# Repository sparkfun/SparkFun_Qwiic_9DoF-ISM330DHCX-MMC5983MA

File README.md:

SparkFun Qwiic 9DoF ISM330DHCX, MMC5983MA
========================================

[*SparkFun_Qwiic_9DoF-ISM330DHCX-MMC5983MA (19895)*](https://www.sparkfun.com/products/19895)

The SparkFun 9DoF IMU Breakout - ISM330DHCX, MMC5983MA (Qwiic) combines the high-performance ISM330DHCX 3D digital accelerometer and gyroscope from STMicroelectronics with the highly sensitive triple-axis magnetometer by MEMSIC to give you an ultra powerful, easy to use, Qwiic enabled breakout board. 

With a full scale acceleration range of ±2/±4/±8/±16 g and a wide angular rate range of ±125/±250/±500/±1000/±2000/±4000 dps, as well as an unmatched set of embedded features (Machine Learning Core, programmable FSM, FIFO, sensor hub, event decoding and interrupts), the ISM330DHCX delivers high performance at very low power. Add to that the MMC5983MA, which can measure magnetic fields within the full scale range of &#177;8 Gauss (G), with 0.25mG/0.0625mG per LSB resolution at 16bits/18bits operation mode and 0.4 mG total RMS noise level and you've got 9 Degrees of Freedom on one tiny little breakout board. 

Utilizing our handy Qwiic system, no soldering is required to connect it to the rest of your system. However, we still have broken out 0.1"-spaced pins in case you prefer to use a breadboard.  
  
Repository Contents
-------------------

* **/Documentation** - Data sheets, additional product information
* **/Hardware** - Eagle design files (.brd, .sch)
* **/Production** - Production panel files (.brd)

Documentation
--------------

* **[6DoF ISM330DHCX Library](https://github.com/sparkfun/SparkFun_6DoF_ISM330DHCX_Arduino_Library)** - Arduino library for the SparkFun Qwiic 6DoF ISM330DHCX.
* **[MMC5983MA Magnetometer Library](https://github.com/sparkfun/SparkFun_MMC5983MA_Magnetometer_Arduino_Library)** - Arduino library for the SparkFun Qwiic MMC5983MA Magnetometer.
* **[Hookup Guide](https://learn.sparkfun.com/tutorials/2616)** - Basic hookup guide for the SparkFun Qwiic 9DoF-ISM330DHCX-MMC5983MA.

License Information
-------------------

This product is _**open source**_! 

Please review the LICENSE.md file for license information. 

If you have any questions or concerns on licensing, please contact technical support on our [SparkFun forums](https://forum.sparkfun.com/viewforum.php?f=152).

Distributed as-is; no warranty is given.

- Your friends at SparkFun.

_<COLLABORATION CREDIT>_

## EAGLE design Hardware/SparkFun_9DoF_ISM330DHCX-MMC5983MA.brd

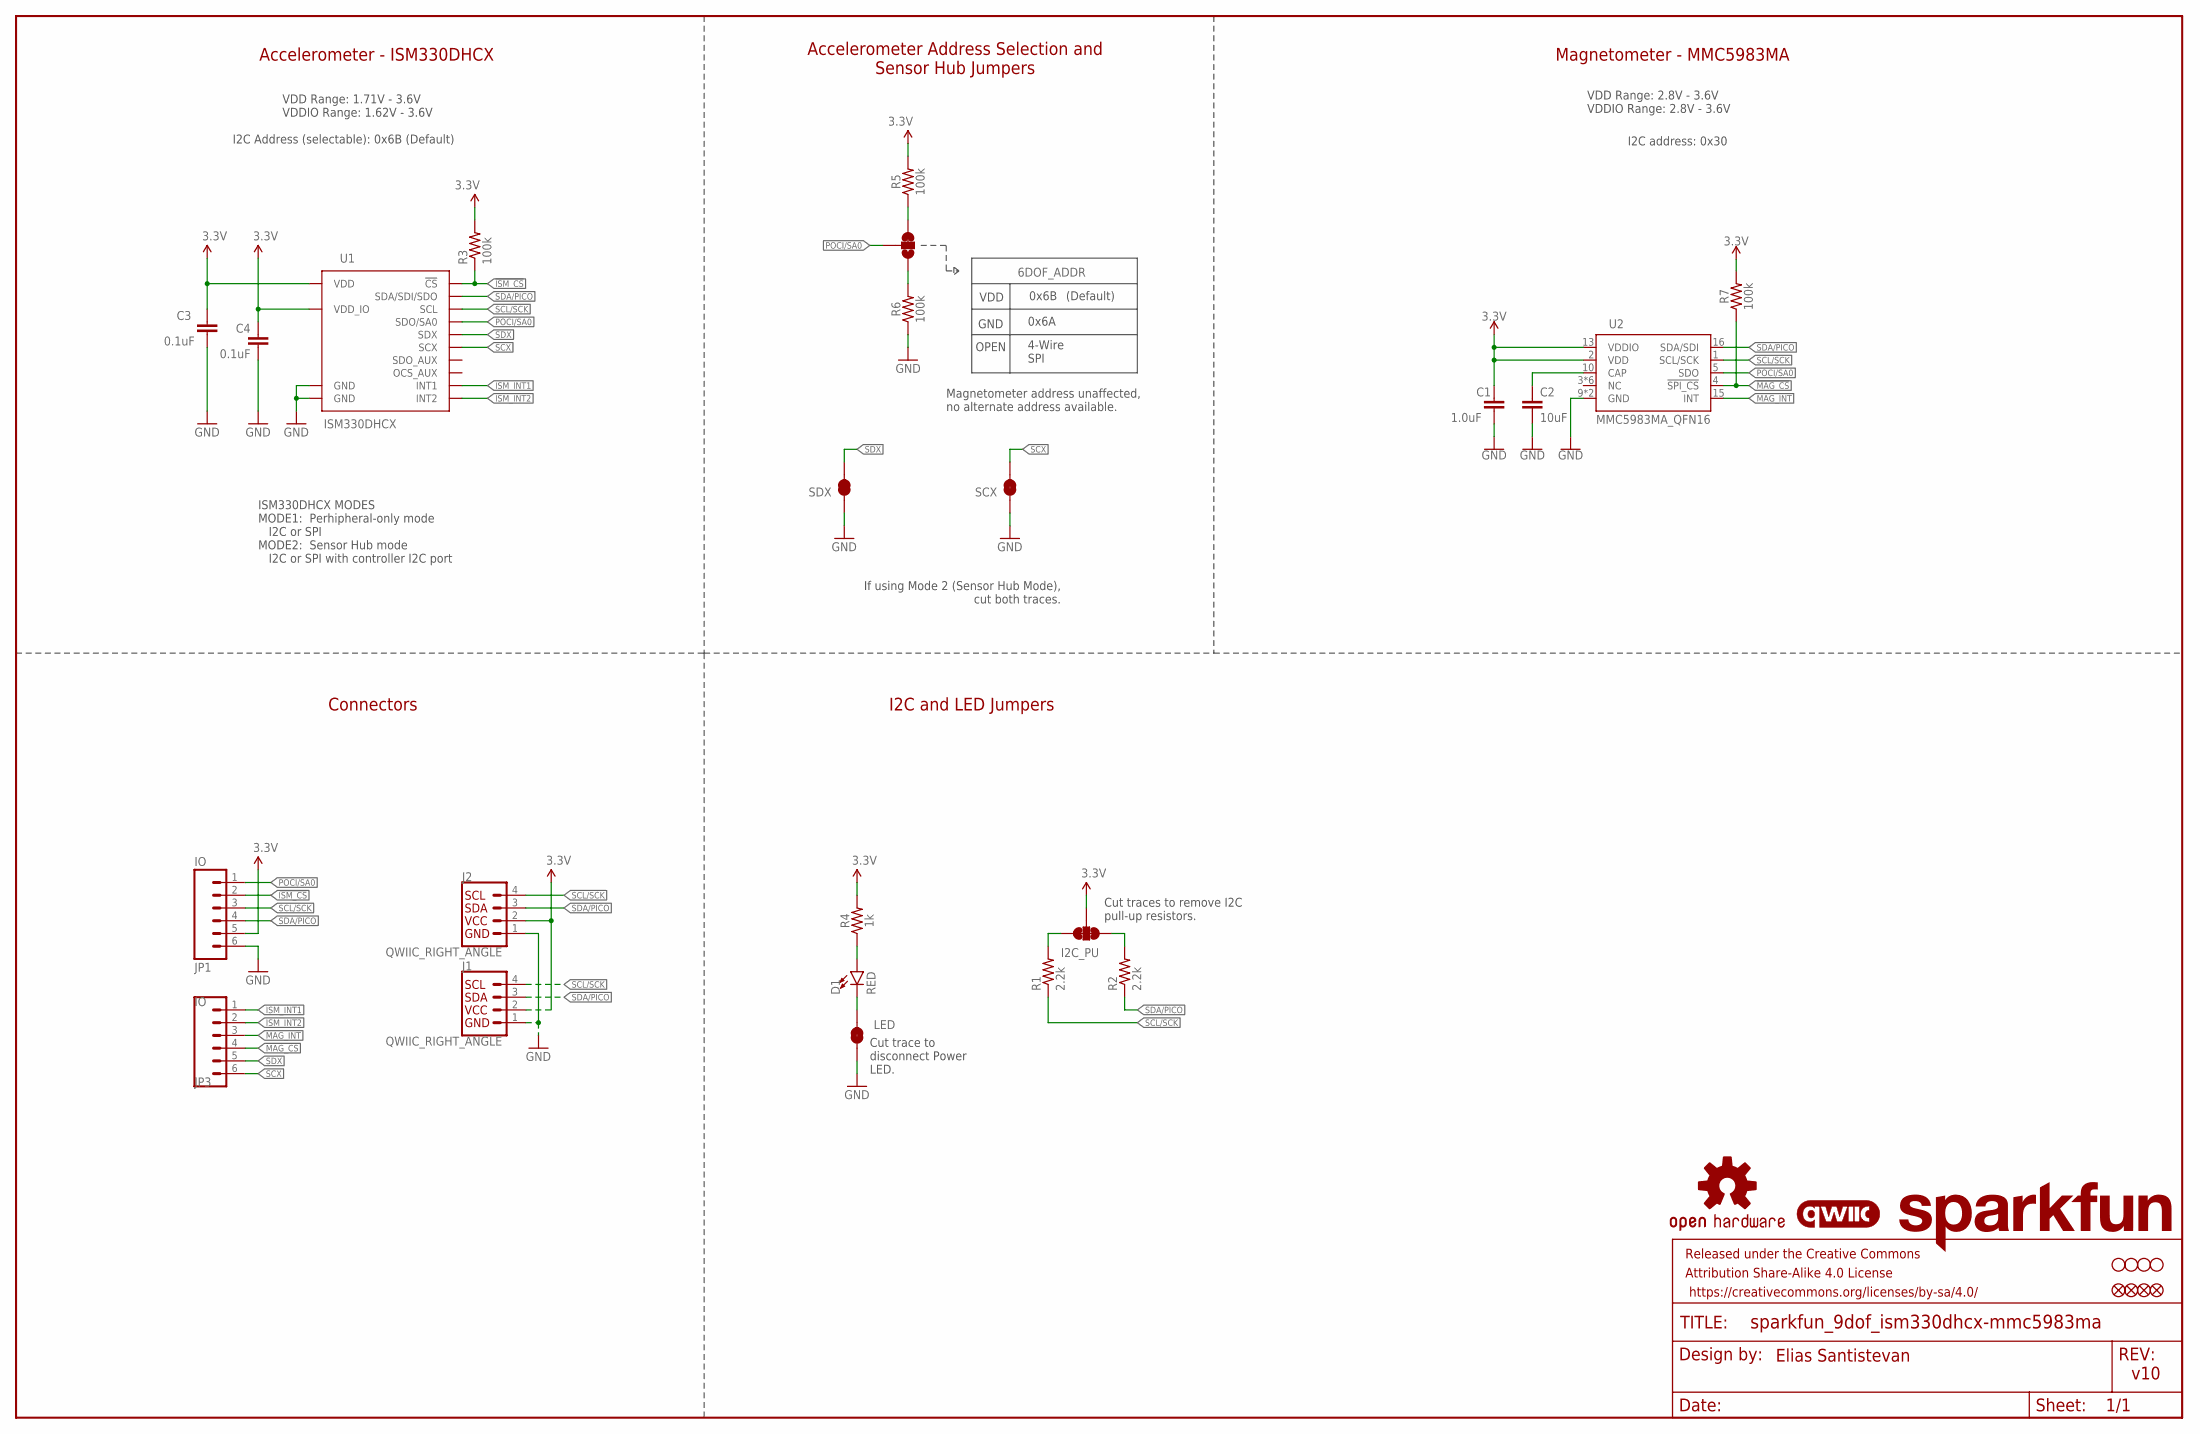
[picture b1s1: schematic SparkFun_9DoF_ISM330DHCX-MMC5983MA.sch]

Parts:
6DOF_ADDR: JUMPER-SMT_3_1-NC_TRACE_SILK; SMT-JUMPER_3_1-NC_TRACE_SILK
C1: 1.0uF; 0603
C2: 10uF; 0603
C3, C4: 0.1uF; 0603
D1: RED; LED-0603
FD1, FD2: FIDUCIALUFIDUCIAL; FIDUCIAL-MICRO
FID1, FID2: FIDUCIALUFIDUCIAL; FIDUCIAL-MICRO
FRAME2: FRAME-LEDGER; CREATIVE_COMMONS
I2C_PU: S_MODE; SMT-JUMPER_3_2-NC_TRACE_SILK
J1, J2: QWIIC_RIGHT_ANGLE; JST04_1MM_RA
JP1, JP3: IO; 1X06_NO_SILK
LED: JUMPER-SMT_2_NC_TRACE_SILK; SMT-JUMPER_2_NC_TRACE_SILK
LOGO1: QWIIC_LOGO_4MM; QWIIC_4MM
LOGO2: OSHW-LOGOMINI; OSHW-LOGO-MINI
LOGO3: SFE_LOGO_NAME.1_INCH; SFE_LOGO_NAME_.1
R1, R2: 2.2k; 0603
R3, R5, R6, R7: 100k; 0603
R4: 1k; 0603
SCX: JUMPER-SMT_2_NC_TRACE_SILK; SMT-JUMPER_2_NC_TRACE_SILK
SDX: JUMPER-SMT_2_NC_TRACE_SILK; SMT-JUMPER_2_NC_TRACE_SILK
STANDOFF1, STANDOFF2, STANDOFF3, STANDOFF4: STAND-OFFTIGHT; STAND-OFF-TIGHT
U1: ISM330DHCX; LGA-14L
U2: MMC5983MA_QFN16; LGA-16-3X3MM-4X4PINS

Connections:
3.3V: C1.1, C3.1, C4.1, I2C_PU.2, J1.2, J2.2, JP1.5, R3.2, R4.2, R5.2, R7.2, U1.P5 (VDD_IO), U1.P8 (VDD), U2.2 (VDD), U2.13 (VDDIO)
!ISM_CS!: JP1.2, R3.1, U1.P12 (!CS!)
!MAG_CS!: JP3.4, R7.1, U2.4 (!SPI_CS!)
CAP: C2.1, U2.10 (CAP)
GND: C1.2, C2.2, C3.2, C4.2, J1.1, J2.1, JP1.6, LED.1, R6.1, SCX.1, SDX.1, U1.P6 (GND), U1.P7 (GND), U2.9 (GND), U2.11 (GND)
ISM_INT1: JP3.1, U1.P4 (INT1)
ISM_INT2: JP3.2, U1.P9 (INT2)
MAG_INT: JP3.3, U2.15 (INT)
unnamed: 6DOF_ADDR.3, R5.1
unnamed: D1.A, R4.1
unnamed: D1.C, LED.2
unnamed: I2C_PU.1, R1.2
unnamed: I2C_PU.3, R2.2
unnamed: 6DOF_ADDR.1, R6.2
POCI/SA0: 6DOF_ADDR.2, JP1.1, U1.P1 (SDO/SA0), U2.5 (SDO)
SCL/SCK: J1.4, J2.4, JP1.3, R1.1, U1.P13 (SCL), U2.1 (SCL/SCK)
SCX: JP3.6, SCX.2, U1.P3 (SCX)
SDA/PICO: J1.3, J2.3, JP1.4, R2.1, U1.P14 (SDA/SDI/SDO), U2.16 (SDA/SDI)
SDX: JP3.5, SDX.2, U1.P2 (SDX)

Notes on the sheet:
Accelerometer - ISM330DHCX
Cut traces to remove I2C pull-up resistors.
VDD Range: 1.71V - 3.6V VDDIO Range: 1.62V - 3.6V
v10
Cut trace to disconnect Power LED.
Connectors
VDD
GND
OPEN
0x6B
0x6A
4-Wire SPI
Elias Santistevan
VDD Range: 2.8V - 3.6V VDDIO Range: 2.8V - 3.6V
Magnetometer - MMC5983MA
Accelerometer Address Selection and Sensor Hub Jumpers
I2C and LED Jumpers
I2C address: 0x30
(Default)
I2C Address (selectable): 0x6B (Default)
ISM330DHCX MODES MODE1: Perhipheral-only mode I2C or SPI MODE2: Sensor Hub mode I2C or SPI with controller I2C port
If using Mode 2 (Sensor Hub Mode), cut both traces.
Magnetometer address unaffected, no alternate address available.

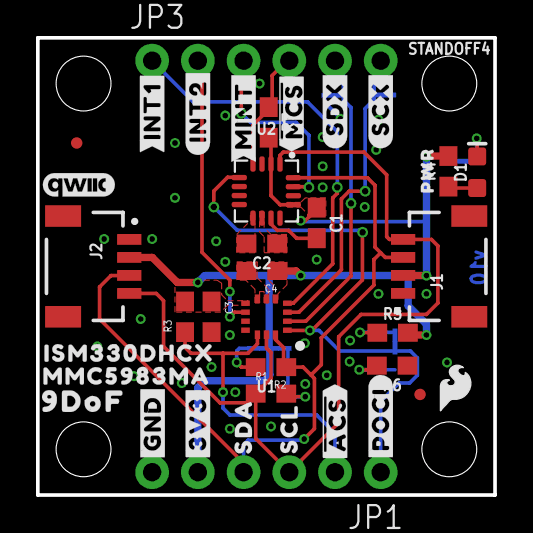
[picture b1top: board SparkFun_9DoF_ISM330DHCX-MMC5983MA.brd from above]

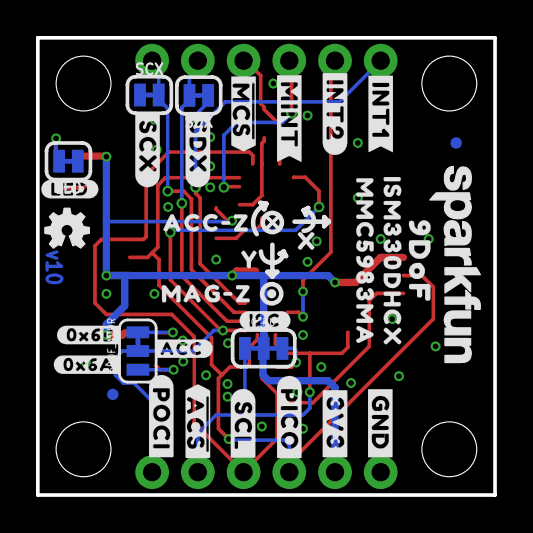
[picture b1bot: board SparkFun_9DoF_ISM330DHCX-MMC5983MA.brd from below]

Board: 2 copper layers, 25.4 x 25.4 mm, 76 parts (33 on the bottom side), 19 nets.

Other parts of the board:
U$1, U$15: #3V3#1
U$2, U$17: #GND#0
U$3, U$7: ISM330DHCX331
U$4: SDA14
U$5: SCL13
U$6: #POCI#11
U$8: #INT1#0
U$9: #INT2#3
U$10: #INT1#2
U$11: #INT2#2
U$12: #MINT#4
U$13: ACC#Z5985
U$14: MAG#Z5984
U$16: #LED#11
U$18: #POCI#12
U$19: ##MCS##5
U$20: #SDX#7
U$21, U$32: MMC5983MA24
U$22: #SCL#5
U$23: #SCX#8
U$24, U$30: 9DOF24
U$25: #I2C#11
U$26: #PICO#13
U$27: ##ACS##6
U$28: PWR8
U$29: SFE_LOGO_FLAME_.1
U$31: #MINT#5
U$33: #0X6A#15
U$34: ##MCS##7
U$35: #SDX#9
U$36: #SCX#11
U$37: X2114
U$38: Y2115
U$39: ##ACS##8
U$40: #0X6B#15
U$41: #ACC#17

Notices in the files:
parts and their libraries:
SparkFun-Aesthetics: Licensing: Creative Commons ShareAlike 4.0 International - https://creativecommons.org/licenses/by-sa/4.0
SparkFun-Aesthetics: Released under the Creative Commons Attribution Share-Alike 4.0 License
SparkFun-Aesthetics: https://creativecommons.org/licenses/by-sa/4.0
